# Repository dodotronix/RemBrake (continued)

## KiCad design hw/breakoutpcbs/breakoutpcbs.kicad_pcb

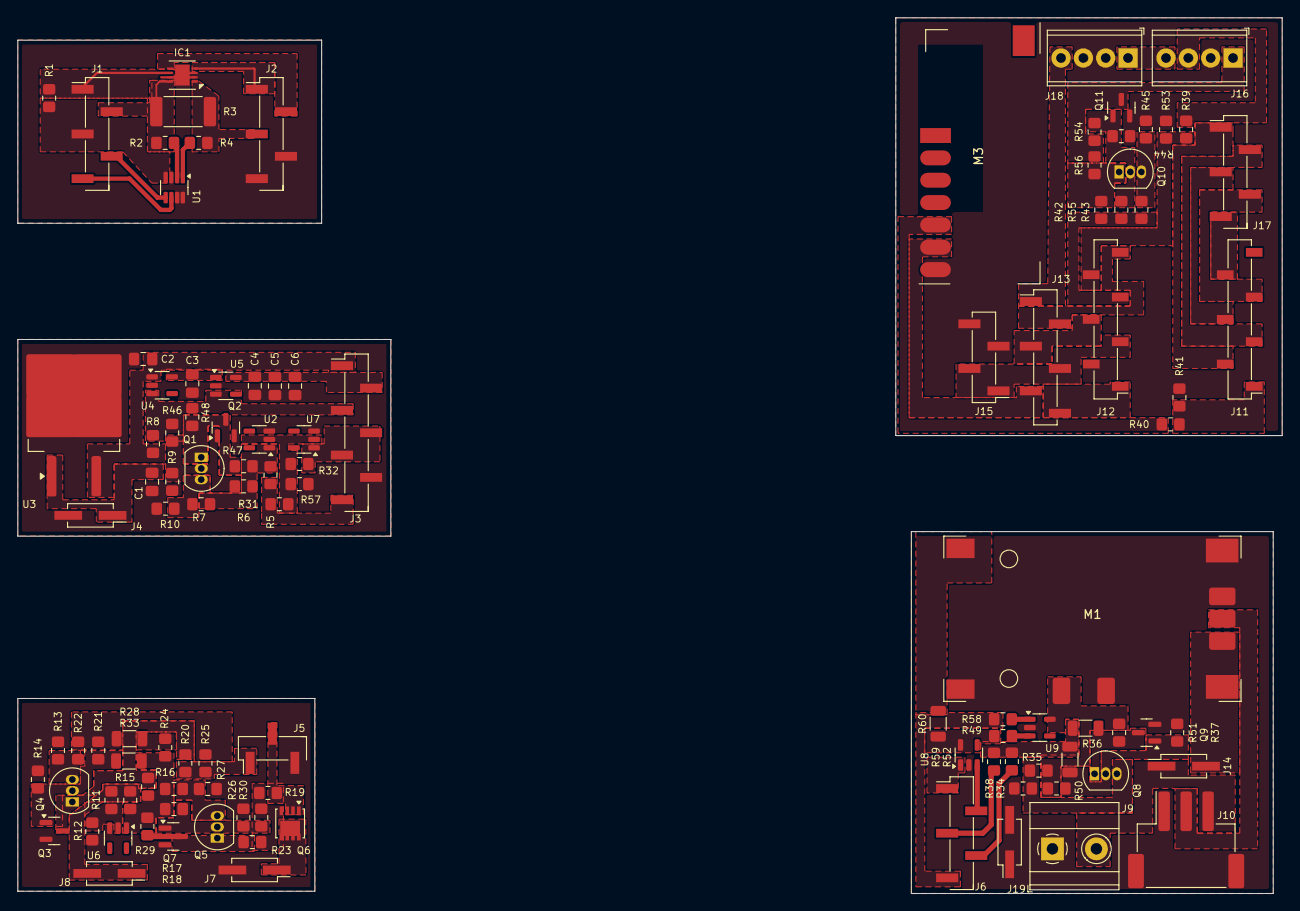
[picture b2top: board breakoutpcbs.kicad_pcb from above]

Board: 2 copper layers, 143.8 x 99.6 mm, 108 parts (0 on the bottom side), 80 nets.

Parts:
C1, C2: 0.1uF; C_0805_2012Metric_Pad1.18x1.45mm_HandSolder
C3: 10uF; C_0805_2012Metric_Pad1.18x1.45mm_HandSolder
C4, C5, C6: 22uF; C_0805_2012Metric_Pad1.18x1.45mm_HandSolder
IC1: LTC2943IDD#TRPBF; DFN-8-1EP_3x3mm_P0.5mm_EP1.66x2.38mm
J1, J2, J6, J17: Conn_01x05; PinHeader_1x05_P2.54mm_Vertical_SMD_Pin1Left
J3: Conn_01x07; PinHeader_1x07_P2.54mm_Vertical_SMD_Pin1Left
J4, J7, J8, J14, J19: Conn_01x02; PinHeader_2x01_P2.54mm_Vertical_SMD
J5: Conn_01x03; PinHeader_1x03_P2.54mm_Vertical_SMD_Pin1Left
J9: Screw_Terminal_01x02; TerminalBlock_Phoenix_MKDS-1,5-2_1x02_P5.00mm_Horizontal
J10: Conn_01x03_MountingPin; JST_XH_S3B-XH-SM4-TB_1x03-1MP_P2.50mm_Horizontal
J11, J12: Conn_01x07; PinSocket_1x07_P2.54mm_Vertical_SMD_Pin1Left
J13: Conn_01x06; PinHeader_1x06_P2.54mm_Vertical_SMD_Pin1Left
J15: Conn_01x04; PinHeader_1x04_P2.54mm_Vertical_SMD_Pin1Left
J16, J18: Screw_Terminal_01x04; TerminalBlock_Phoenix_MPT-0,5-4-2.54_1x04_P2.54mm_Horizontal
M1: USBC_charger
M3: RF_controller
Q1, Q4, Q5, Q8, Q10: BC337; TO-92_Inline
Q2, Q3, Q7, Q9, Q11: BC847; SOT-23
Q6: SiS415DNT; Vishay_PowerPAK_1212-8_Single
R1, R5, R8, R15, R19, R23, R30, R32, R49, R52, R57: 10k; R_0805_2012Metric_Pad1.20x1.40mm_HandSolder
R2, R4: 10; R_0805_2012Metric_Pad1.20x1.40mm_HandSolder
R3: 001R; R_2512_6332Metric_Pad1.40x3.35mm_HandSolder
R6, R7, R10, R13, R16, R20, R24, R25, R27, R31, R38, R45, R46, R47, R48, R54, R56: 0R; R_0805_2012Metric_Pad1.20x1.40mm_HandSolder
R9, R14, R17, R18, R21, R22, R26, R29, R34, R35, R37, R42, R43, R44, R51, R55: 4k2; R_0805_2012Metric_Pad1.20x1.40mm_HandSolder
R11: 91k; R_0805_2012Metric_Pad1.20x1.40mm_HandSolder
R12: 67k; R_0805_2012Metric_Pad1.20x1.40mm_HandSolder
R28, R33, R36, R50, R60: 0R; R_1206_3216Metric
R39: 12k; R_0805_2012Metric_Pad1.20x1.40mm_HandSolder
R40: 2k7; R_0805_2012Metric_Pad1.20x1.40mm_HandSolder
R41, R53: 4k7; R_0805_2012Metric_Pad1.20x1.40mm_HandSolder
R58, R59: 200R; R_0805_2012Metric_Pad1.20x1.40mm_HandSolder
U1: INA219BxDCN; SOT-23-8
U2, U6, U7: BD48ExxG; SOT-23-5
U3: L7805; TO-263-2
U4: XC6220B331MR; SOT-23-5
U5, U8, U9: MAX40200AUK; SOT-23-5

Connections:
+3V3: J1.3, R1.1, U1.4 (VS)
+3V3_1: C4.1, C5.1, C6.1, J3.2, U5.5 (OUT)
+3V3_2: J6.4, R52.1
+3V3_3: J12.3, J13.4, J15.1, J15.2
+5V: C2.1, J3.1, R8.2, U3.3 (OUT), U4.1 (VIN)
+5V_1: J13.5, M3.6 (V+)
+7.5V: J7.1, Q6.5 (D)
+7V5_1: J13.1, J18.4
/battery_charger/CHARGED (GREEN): J6.5, R58.1
/battery_charger/CHARGING (BLUE): J6.3, R59.2
/battery_charger/EN2: J6.2, U8.3 (EN)
/battery_charger/VBUS1: J6.1, U8.1 (VDD)
/break_control/BALARM1: J11.2, J17.1
/break_control/BUTTON: J16.3, R39.1
/break_control/BUZZ: J12.5, R42.1, R43.1, R55.2
/break_control/BUZZER: J16.1, Q11.3 (C), R54.2, R56.2
/break_control/CHARGING1: J12.4, J13.3
/break_control/DCKI: J11.4, J17.3
/break_control/DI: J11.3, J17.2
/break_control/RF SWITCH: J11.1, R40.1, R41.2
/break_control/SCL: J11.6, J17.5
/break_control/SDA: J11.5, J17.4
/break_control/SERVO: J12.7, J13.2
/break_control/VBUS2: J12.1, J13.6
/break_control/VEXT: J16.4, J18.1
/power_manager_bb/BALARM: IC1.6 (~ALCC), J1.1, R1.2
/power_switch_bbA/EN1: J5.1, R20.1, R25.1
/power_switch_bbA/ONOFF: J8.1, J8.2, R11.2, R15.2
/power_switch_bbA/VBATT: J5.2, Q6.1 (S), Q6.2 (S), Q6.3 (S), R19.1
/power_switch_bbB/EN: J3.4, J3.5, R32.1, U7.1 (VOUT)
/power_switch_bbB/ONOFF: C1.1, J4.1, U3.1 (IN)
/power_switch_bbB/RUNNING: J3.3, R8.1, R46.2, R48.2, U4.3 (CE), U5.3 (EN)
/power_switch_bbB/VBUS: J3.7, R5.2, R31.1
GND: IC1.2 (GND_1), IC1.3 (GND_2), IC1.7 (GND_3), IC1.9 (EP), J2.4, J2.5, U1.3 (GND), U1.7 (A0), U1.8 (A1)
GND1: J5.3, J7.2, Q3.2 (E), Q7.2 (E), R12.1, R13.1, R14.1, R26.1, R27.1, U6.3 (GND)
GND2: C1.2, C2.2, C3.2, C4.2, C5.2, C6.2, J3.6, J4.2, Q2.2 (E), R9.1, R10.1, R57.2, U2.3 (GND), U3.2 (GND), U4.2 (GND), U5.2 (GND), U7.3 (GND)
GND3: J9.1, J10.1, J10.MP (MountPin), J19.1, J19.2, M1.2 (GND), M1.5 (BAT-), Q9.2 (E), R37.1, R38.1, U8.2 (GND), U9.2 (GND)
GND4: J12.2, J15.3, J15.4, J16.2, J18.2, J18.3, M3.7 (GND), Q11.2 (E), R41.1, R44.1, R45.1, R53.2
unnamed: IC1.4 (SCL), J2.1
unnamed: IC1.5 (SDA), J2.2
unnamed: IC1.1 (SENSE+), J2.3, R3.2, R4.1
unnamed: IC1.8 (SENSE-), J1.2, R2.1, R3.1
unnamed: J1.4, U1.5 (SCL)
unnamed: J1.5, U1.6 (SDA)
unnamed: J10.2, M1.4 (BM)
unnamed: J9.2, J10.3, J14.1
unnamed: J12.6, R39.2, R53.1
unnamed: J14.2, M1.3 (BAT+)
unnamed: M1.6 (LED), R34.1, R35.1, R51.1, U9.5 (OUT)
unnamed: M1.1 (Vin), R60.1
unnamed: M3.5 (D0), R40.2
unnamed: Q1.2 (B), Q2.1 (B), R6.2, R9.2, R46.1
unnamed: Q1.1 (C), Q2.3 (C), R47.1, R48.1
unnamed: Q1.3 (E), R7.2, R10.2
unnamed: Q3.1 (B), Q4.2 (B), R14.2, R21.2, R33.1
unnamed: Q3.3 (C), Q4.1 (C), R16.1, R20.2
unnamed: Q4.3 (E), R13.2, R22.2
unnamed: Q5.2 (B), Q7.1 (B), R17.2, R26.2, R30.1
unnamed: Q5.1 (C), Q7.3 (C), R23.1, R29.2
unnamed: Q5.3 (E), R18.2, R27.2
unnamed: Q6.4 (G), R19.2, R23.2, R30.2
unnamed: Q8.2 (B), Q9.1 (B), R34.2, R37.2, R50.2
unnamed: Q8.1 (C), Q9.3 (C), R36.2, R51.2
unnamed: Q8.3 (E), R35.2, R38.2
unnamed: Q10.2 (B), Q11.1 (B), R42.2, R44.2, R54.1
unnamed: Q10.1 (C), R55.1, R56.1
unnamed: Q10.3 (E), R43.2, R45.2
unnamed: R21.1, R22.1, R25.2, R28.1
unnamed: R24.1, R28.2
unnamed: R36.1, R50.1, R52.2, R59.1
unnamed: R4.2, U1.1 (IN+)
unnamed: R2.2, U1.2 (IN-)
unnamed: R31.2, R32.2, R57.1, U2.2 (VDD), U7.2 (VDD)
unnamed: R5.1, R6.1, R7.1, R47.2, U2.1 (VOUT)
unnamed: C3.1, U4.5 (VOUT), U5.1 (VDD)
unnamed: R11.1, R12.2, U6.2 (VDD)
unnamed: R15.1, R16.2, R17.1, R18.1, R24.2, R29.1, R33.2, U6.1 (VOUT)
unnamed: R49.1, R60.2, U8.5 (OUT)
unnamed: R49.2, U9.3 (EN)
unnamed: R58.2, U9.1 (VDD)

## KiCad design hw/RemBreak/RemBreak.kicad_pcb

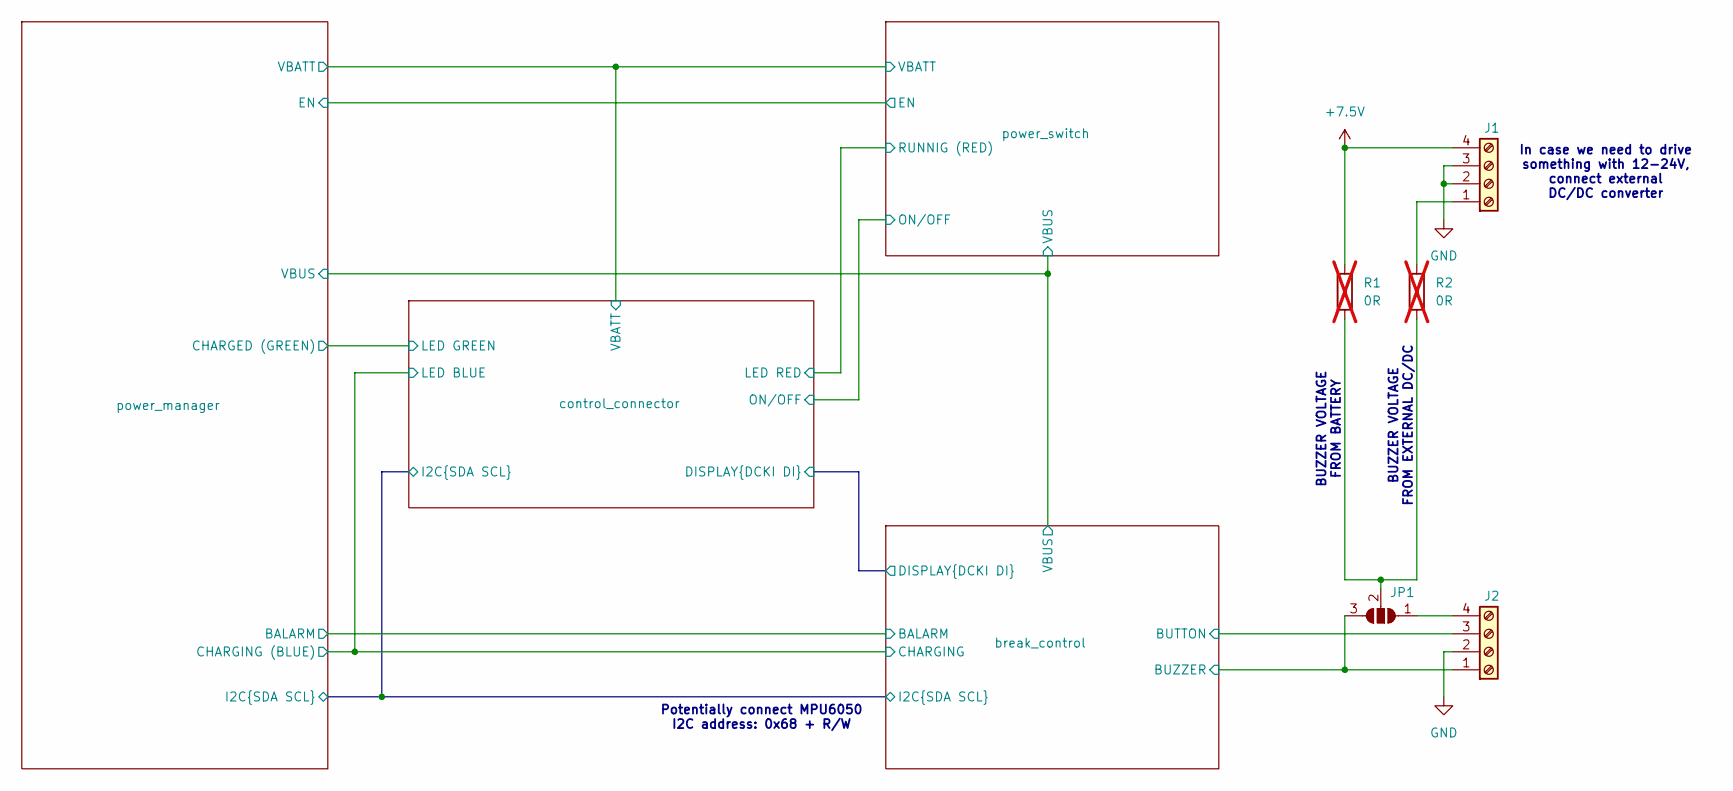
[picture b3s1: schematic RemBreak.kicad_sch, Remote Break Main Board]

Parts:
J1, J2: Screw_Terminal_01x04; TerminalBlock_Phoenix_MPT-0,5-4-2.54_1x04_P2.54mm_Horizontal
JP1: SolderJumper_3_Open; SolderJumper-3_P1.3mm_Open_RoundedPad1.0x1.5mm
R1, R2: 0R; R_0805_2012Metric_Pad1.20x1.40mm_HandSolder; not fitted

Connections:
+7.5V: J1.4, R1.1; also elsewhere on the board
/break_control/BUTTON: J2.3; also elsewhere on the board
/break_control/BUZZER: J2.1, JP1.3 (B); also elsewhere on the board
GND: J1.2, J1.3, J2.2; also elsewhere on the board
unnamed: J1.1, R2.1
unnamed: J2.4, JP1.1 (A)
unnamed: JP1.2 (C), R1.2, R2.2

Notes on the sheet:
Potentially connect MPU6050 I2C address: 0x68 + R/W
BUZZER VOLTAGE FROM BATTERY
BUZZER VOLTAGE FROM EXTERNAL DC/DC
In case we need to drive something with 12-24V, connect external DC/DC converter

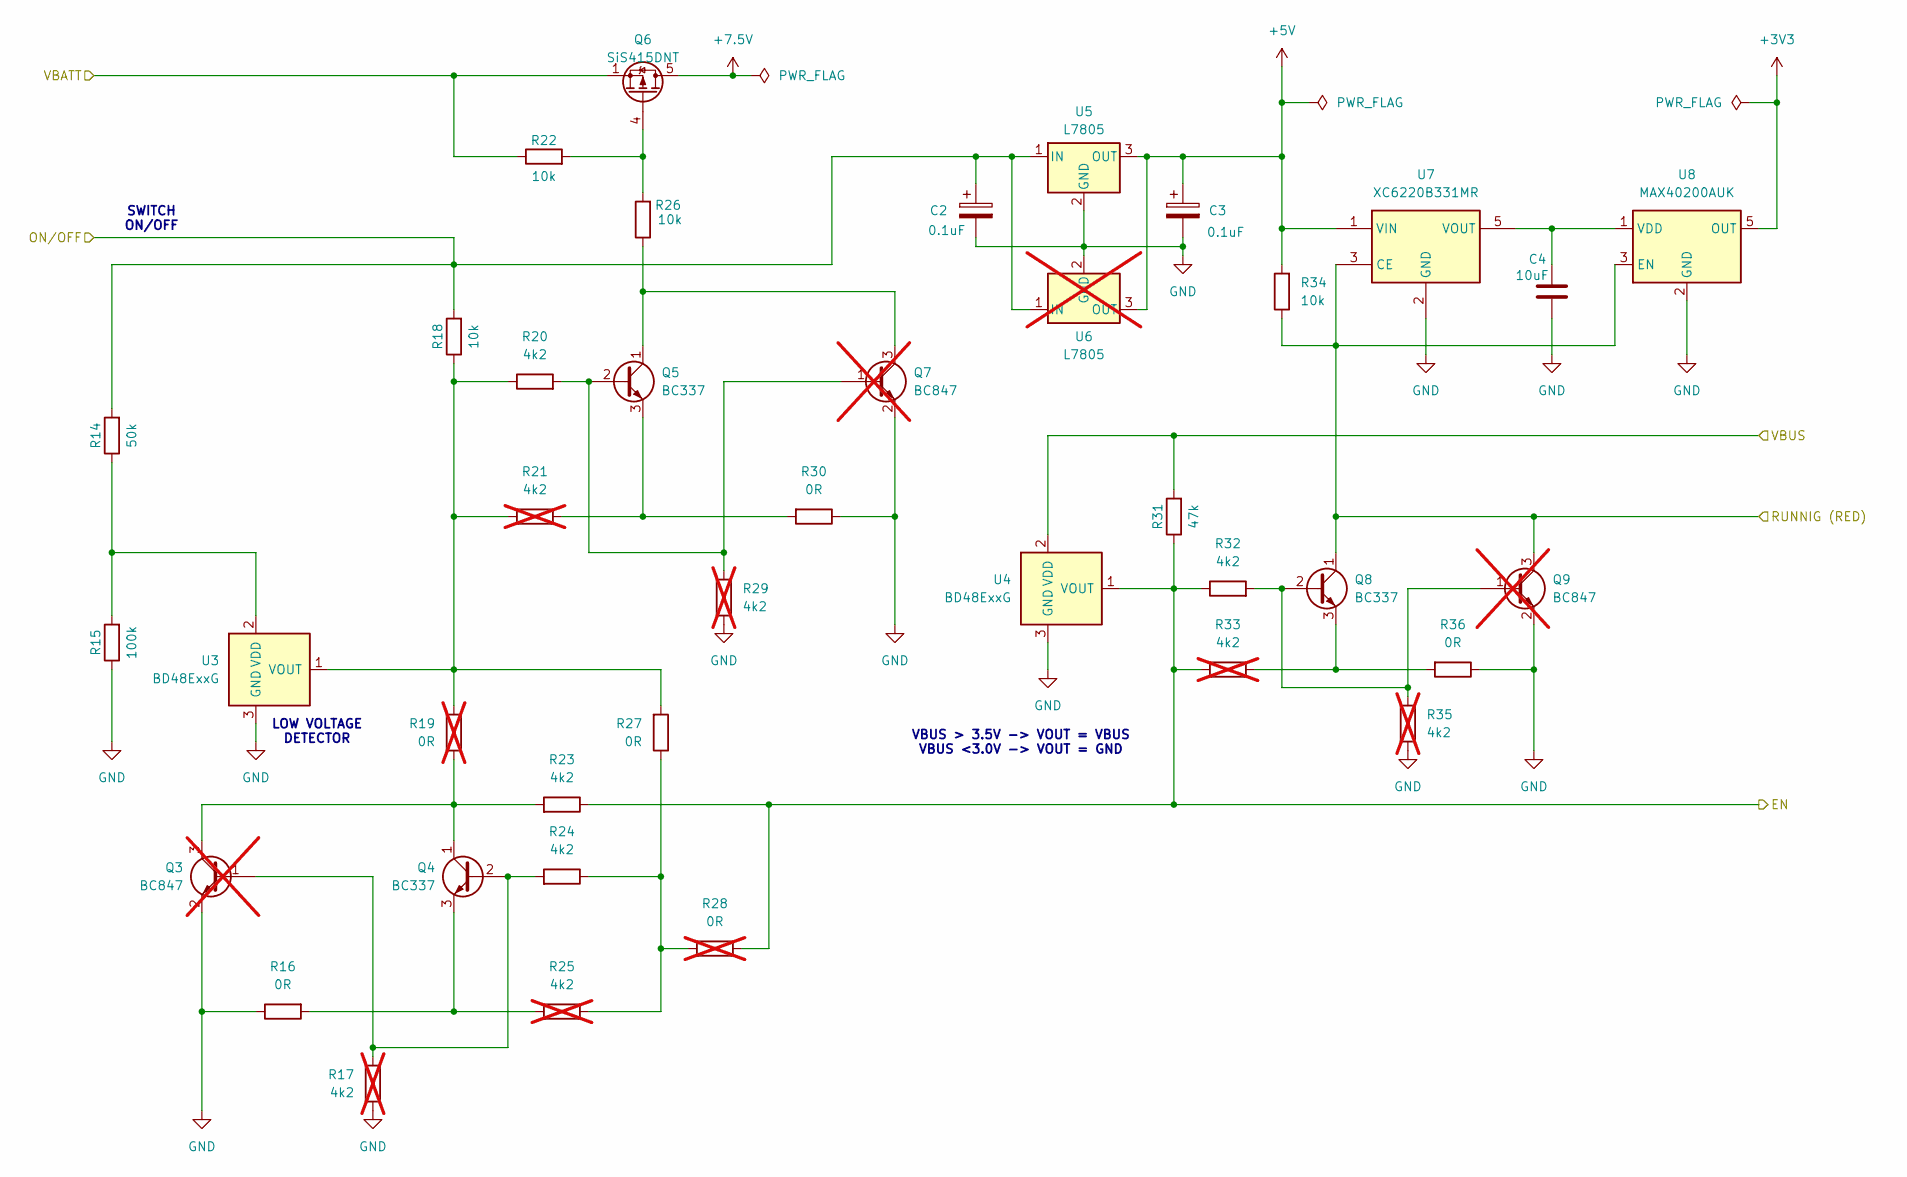
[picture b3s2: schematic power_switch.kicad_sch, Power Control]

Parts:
C2, C3: 0.1uF; C_0805_2012Metric_Pad1.18x1.45mm_HandSolder
C4: 10uF; C_0805_2012Metric_Pad1.18x1.45mm_HandSolder
Q3, Q7, Q9: BC847; SOT-23; not fitted
Q4, Q5, Q8: BC337; TO-92_Inline
Q6: SiS415DNT; Vishay_PowerPAK_1212-8_Single
R14: 50k; R_0805_2012Metric_Pad1.20x1.40mm_HandSolder
R15: 100k; R_0805_2012Metric_Pad1.20x1.40mm_HandSolder
R16, R27, R30, R36: 0R; R_0805_2012Metric_Pad1.20x1.40mm_HandSolder
R17, R21, R25, R29, R33, R35: 4k2; R_0805_2012Metric_Pad1.20x1.40mm_HandSolder; not fitted
R18, R22, R26, R34: 10k; R_0805_2012Metric_Pad1.20x1.40mm_HandSolder
R19, R28: 0R; R_0805_2012Metric_Pad1.20x1.40mm_HandSolder; not fitted
R20, R23, R24, R32: 4k2; R_0805_2012Metric_Pad1.20x1.40mm_HandSolder
R31: 47k; R_0805_2012Metric_Pad1.20x1.40mm_HandSolder
U3, U4: BD48ExxG; SOT-23-5
U5: L7805; TO-263-2
U6: L7805; TO-220-3_Vertical; not fitted
U7: XC6220B331MR; SOT-23-5
U8: MAX40200AUK; SOT-23-5

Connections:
+3V3: U8.5 (OUT); also elsewhere on the board
+5V: C3.1, R34.2, U5.3 (OUT), U6.3 (OUT), U7.1 (VIN); also elsewhere on the board
+7.5V: Q6.5 (D); also elsewhere on the board
/break_control/VBUS: R31.2, U4.2 (VDD); also elsewhere on the board
/control_connector/LED RED: Q8.1 (C), Q9.3 (C), R34.1, U7.3 (CE), U8.3 (EN); also elsewhere on the board
/control_connector/ONOFF: C2.1, R14.2, R18.2, U5.1 (IN), U6.1 (IN); also elsewhere on the board
/control_connector/VBATT: Q6.1 (S), Q6.2 (S), Q6.3 (S), R22.1; also elsewhere on the board
/power_manager/EN: R23.1, R28.1, R31.1, R32.1, R33.1, U4.1 (VOUT); also elsewhere on the board
GND: C2.2, C3.2, C4.2, Q3.2 (E), Q7.2 (E), Q9.2 (E), R15.1, R16.1, R17.1, R29.1, R30.1, R35.1, R36.1, U3.3 (GND), U4.3 (GND), U5.2 (GND), U6.2 (GND), U7.2 (GND), U8.2 (GND); also elsewhere on the board
unnamed: Q3.1 (B), Q4.2 (B), R17.2, R24.2
unnamed: Q3.3 (C), Q4.1 (C), R19.1, R23.2
unnamed: Q4.3 (E), R16.2, R25.2
unnamed: Q5.2 (B), Q7.1 (B), R20.2, R29.2
unnamed: Q5.1 (C), Q7.3 (C), R26.1
unnamed: Q5.3 (E), R21.2, R30.2
unnamed: Q6.4 (G), R22.2, R26.2
unnamed: Q8.2 (B), Q9.1 (B), R32.2, R35.2
unnamed: Q8.3 (E), R33.2, R36.2
unnamed: R24.1, R25.1, R27.1, R28.2
unnamed: R14.1, R15.2, U3.2 (VDD)
unnamed: R18.1, R19.2, R20.1, R21.1, R27.2, U3.1 (VOUT)
unnamed: C4.1, U7.5 (VOUT), U8.1 (VDD)

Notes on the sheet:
VBUS > 3.5V -> VOUT = VBUS VBUS <3.0V -> VOUT = GND
LOW VOLTAGE DETECTOR
SWITCH ON/OFF

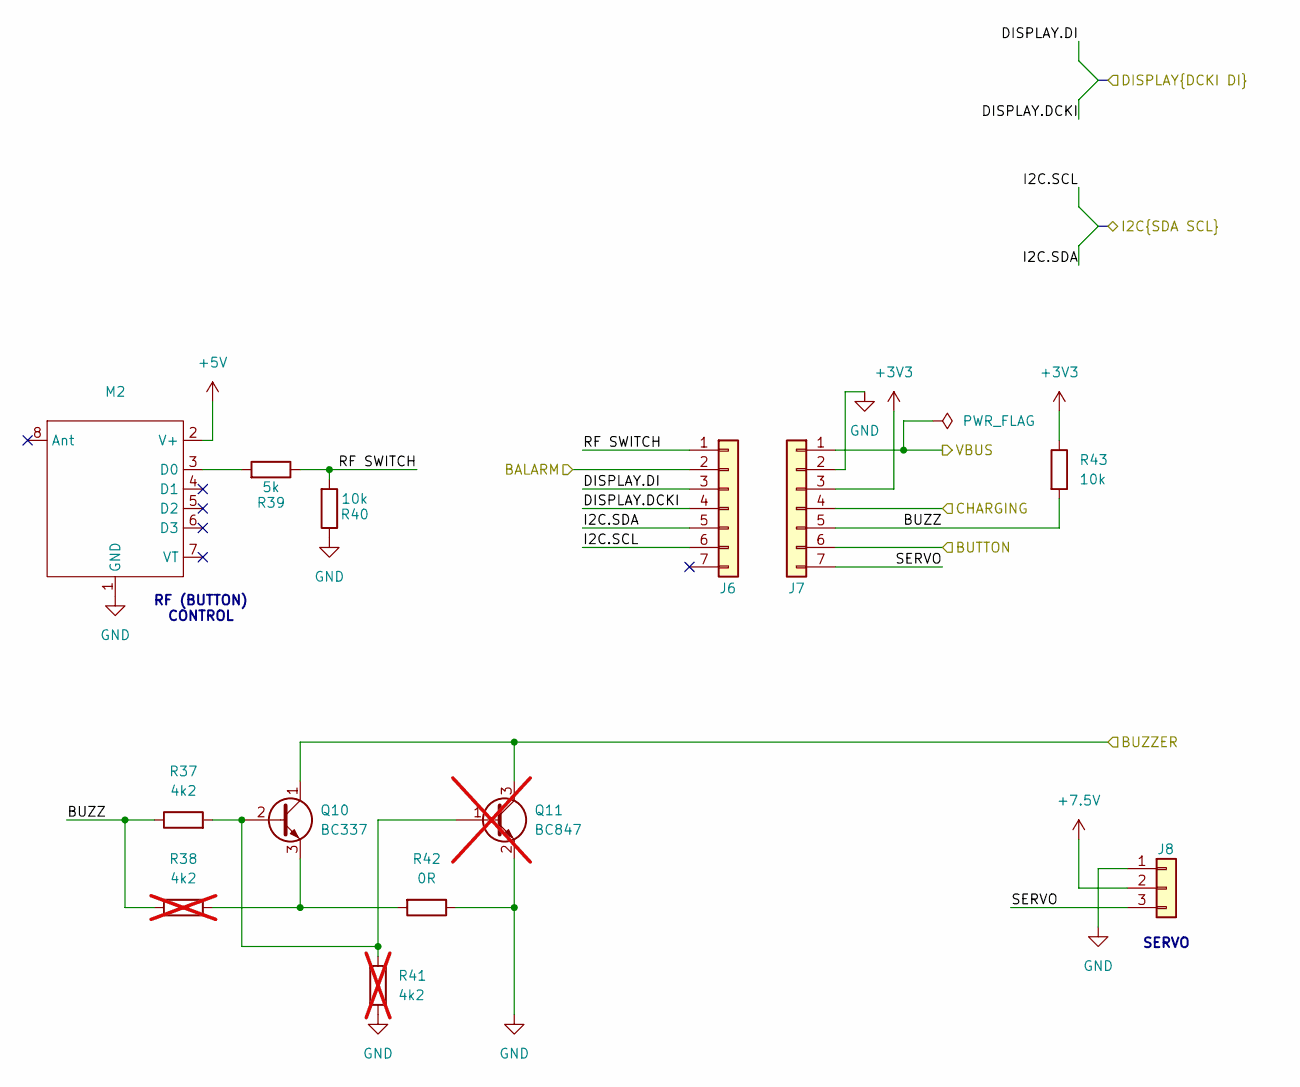
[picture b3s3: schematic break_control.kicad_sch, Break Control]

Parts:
J6, J7: Conn_01x07; PinSocket_1x07_P2.54mm_Vertical_SMD_Pin1Left
J8: Conn_01x03; PinHeader_1x03_P2.54mm_Vertical_SMD_Pin1Left
M2: RF_controller
Q10: BC337; TO-92_Inline
Q11: BC847; SOT-23; not fitted
R37: 4k2; R_0805_2012Metric_Pad1.20x1.40mm_HandSolder
R38, R41: 4k2; R_0805_2012Metric_Pad1.20x1.40mm_HandSolder; not fitted
R39: 5k; R_0805_2012Metric_Pad1.20x1.40mm_HandSolder
R40, R43: 10k; R_0805_2012Metric_Pad1.20x1.40mm_HandSolder
R42: 0R; R_0805_2012Metric_Pad1.20x1.40mm_HandSolder

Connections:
+3V3: J7.3, R43.1; also elsewhere on the board
+5V: M2.2 (V+); also elsewhere on the board
+7.5V: J8.2; also elsewhere on the board
/break_control/BALARM: J6.2; also elsewhere on the board
/break_control/BUTTON: J7.6; also elsewhere on the board
/break_control/BUZZ: J7.5, R37.1, R38.1, R43.2
/break_control/BUZZER: Q10.1 (C), Q11.3 (C); also elsewhere on the board
/break_control/DISPLAY.DCKI: J6.4; also elsewhere on the board
/break_control/DISPLAY.DI: J6.3; also elsewhere on the board
/break_control/I2C.SCL: J6.6; also elsewhere on the board
/break_control/I2C.SDA: J6.5; also elsewhere on the board
/break_control/RF SWITCH: J6.1, R39.1, R40.2
/break_control/SERVO: J7.7, J8.3
/break_control/VBUS: J7.1; also elsewhere on the board
/control_connector/LED BLUE: J7.4; also elsewhere on the board
GND: J7.2, J8.1, M2.1 (GND), Q11.2 (E), R40.1, R41.1, R42.1; also elsewhere on the board
unnamed: M2.3 (D0), R39.2
unnamed: Q10.2 (B), Q11.1 (B), R37.2, R41.2
unnamed: Q10.3 (E), R38.2, R42.2

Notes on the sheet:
SERVO
RF (BUTTON) CONTROL

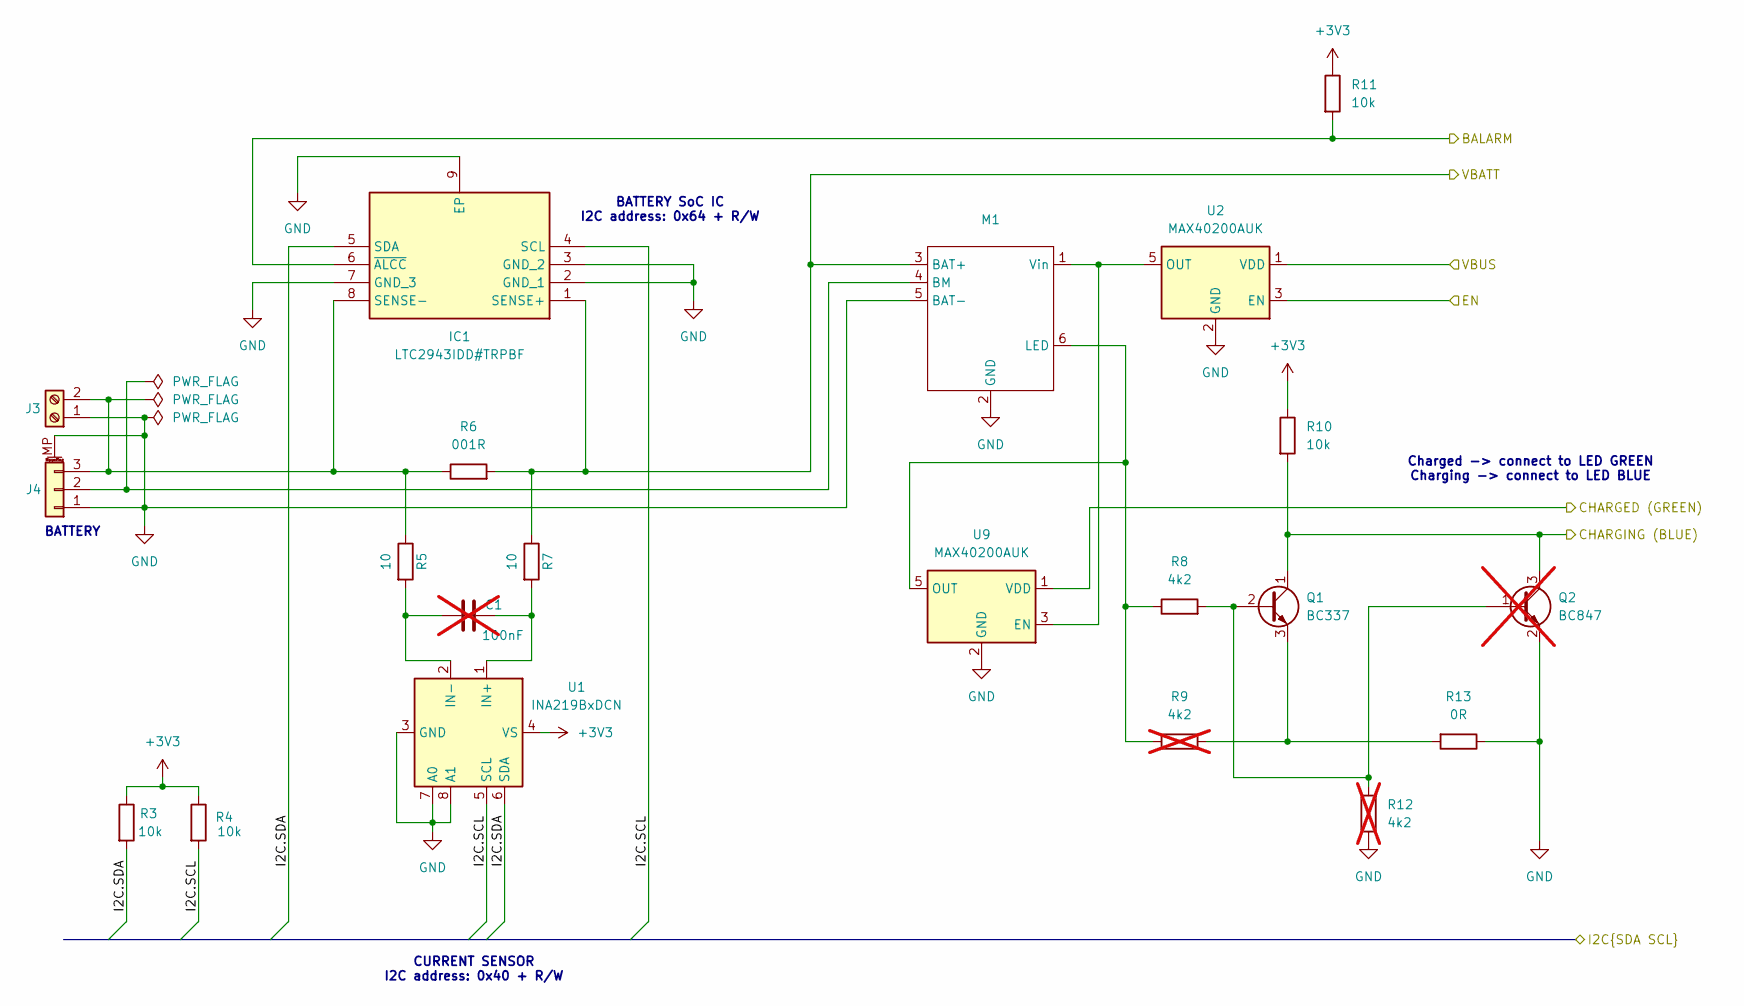
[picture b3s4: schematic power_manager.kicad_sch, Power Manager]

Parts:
C1: 100nF; C_0805_2012Metric_Pad1.18x1.45mm_HandSolder; not fitted
IC1: LTC2943IDD#TRPBF; DFN-8-1EP_3x3mm_P0.5mm_EP1.66x2.38mm; Mouser Part Number 584-LTC2943IDD#TRPBF
J3: Screw_Terminal_01x02; TerminalBlock_Phoenix_MKDS-1,5-2_1x02_P5.00mm_Horizontal
J4: Conn_01x03_MountingPin; JST_XH_S3B-XH-SM4-TB_1x03-1MP_P2.50mm_Horizontal
M1: USBC_charger
Q1: BC337; TO-92_Inline
Q2: BC847; SOT-23; not fitted
R3, R4, R10, R11: 10k; R_0805_2012Metric_Pad1.20x1.40mm_HandSolder
R5, R7: 10; R_0805_2012Metric_Pad1.20x1.40mm_HandSolder
R6: 001R; R_2512_6332Metric_Pad1.40x3.35mm_HandSolder
R8: 4k2; R_0805_2012Metric_Pad1.20x1.40mm_HandSolder
R9, R12: 4k2; R_0805_2012Metric_Pad1.20x1.40mm_HandSolder; not fitted
R13: 0R; R_0805_2012Metric_Pad1.20x1.40mm_HandSolder
U1: INA219BxDCN; SOT-23-8
U2, U9: MAX40200AUK; SOT-23-5

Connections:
+3V3: R3.1, R4.1, R10.1, R11.1, U1.4 (VS); also elsewhere on the board
/break_control/BALARM: IC1.6 (~ALCC), R11.2; also elsewhere on the board
/break_control/I2C.SCL: IC1.4 (SCL), R4.2, U1.5 (SCL); also elsewhere on the board
/break_control/I2C.SDA: IC1.5 (SDA), R3.2, U1.6 (SDA); also elsewhere on the board
/break_control/VBUS: U2.1 (VDD); also elsewhere on the board
/control_connector/LED BLUE: Q1.1 (C), Q2.3 (C), R10.2; also elsewhere on the board
/control_connector/VBATT: IC1.1 (SENSE+), M1.3 (BAT+), R6.2, R7.1; also elsewhere on the board
/power_manager/EN: U2.3 (EN); also elsewhere on the board
GND: IC1.2 (GND_1), IC1.3 (GND_2), IC1.7 (GND_3), IC1.9 (EP), J3.1, J4.1, J4.MP (MountPin), M1.2 (GND), M1.5 (BAT-), Q2.2 (E), R12.1, R13.1, U1.3 (GND), U1.7 (A0), U1.8 (A1), U2.2 (GND), U9.2 (GND); also elsewhere on the board
unnamed: IC1.8 (SENSE-), J3.2, J4.3, R5.1, R6.1
unnamed: J4.2, M1.4 (BM)
unnamed: M1.1 (Vin), U2.5 (OUT), U9.3 (EN)
unnamed: Q1.2 (B), Q2.1 (B), R8.2, R12.2
unnamed: Q1.3 (E), R9.2, R13.2
unnamed: C1.2, R7.2, U1.1 (IN+)
unnamed: C1.1, R5.2, U1.2 (IN-)

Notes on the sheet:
CURRENT SENSOR I2C address: 0x40 + R/W
BATTERY SoC IC I2C address: 0x64 + R/W
Charged -> connect to LED GREEN Charging -> connect to LED BLUE
BATTERY

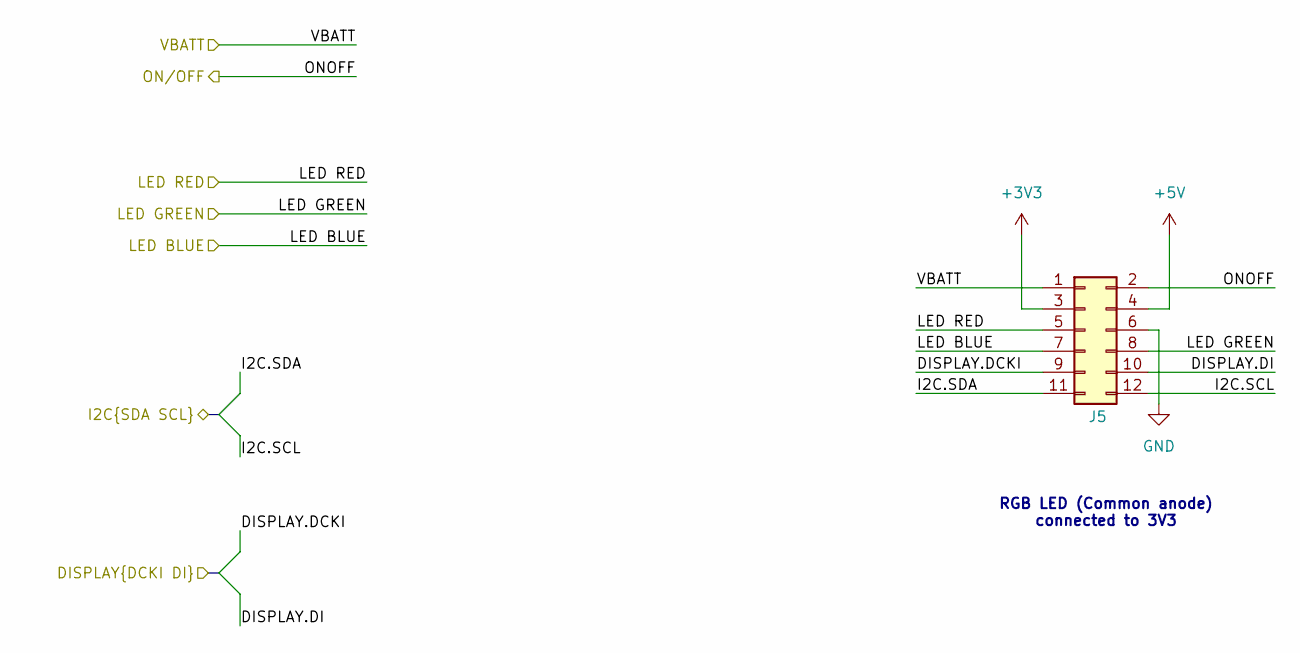
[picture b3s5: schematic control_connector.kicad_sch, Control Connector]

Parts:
J5: Conn_02x06_Odd_Even; SAMTEC_TSM-106-01-L-DH-P-TR

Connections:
+3V3: J5.3; also elsewhere on the board
+5V: J5.4; also elsewhere on the board
/break_control/DISPLAY.DCKI: J5.9; also elsewhere on the board
/break_control/DISPLAY.DI: J5.10; also elsewhere on the board
/break_control/I2C.SCL: J5.12; also elsewhere on the board
/break_control/I2C.SDA: J5.11; also elsewhere on the board
/control_connector/LED BLUE: J5.7; also elsewhere on the board
/control_connector/LED RED: J5.5; also elsewhere on the board
/control_connector/ONOFF: J5.2; also elsewhere on the board
/control_connector/VBATT: J5.1; also elsewhere on the board
GND: J5.6; also elsewhere on the board

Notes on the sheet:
RGB LED (Common anode) connected to 3V3

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
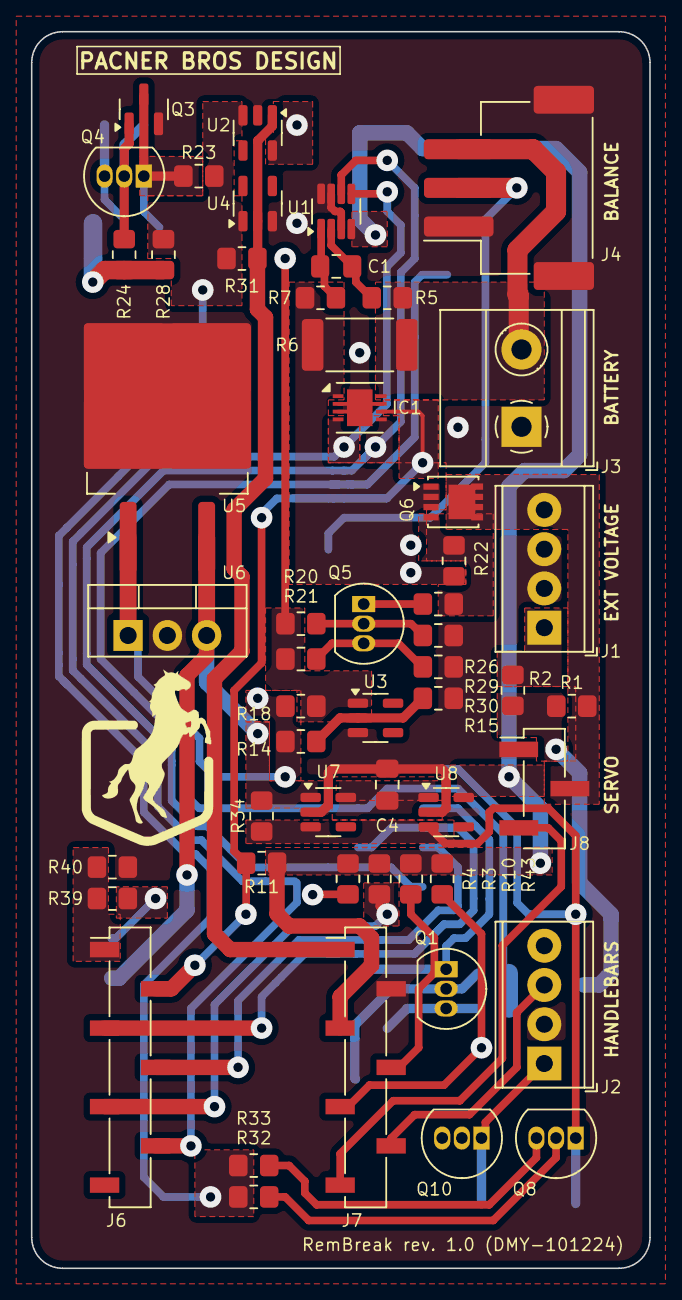
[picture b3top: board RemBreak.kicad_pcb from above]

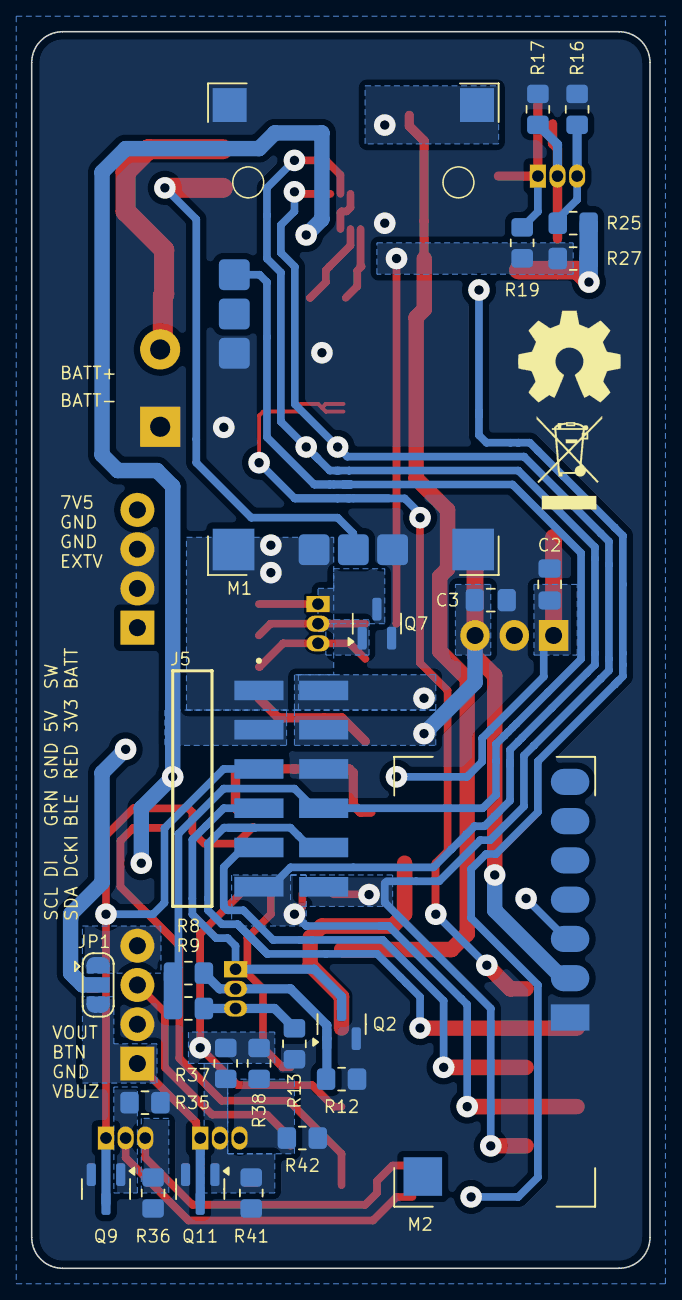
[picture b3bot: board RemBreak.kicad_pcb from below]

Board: 2 copper layers, 40.0 x 80.0 mm, 78 parts (25 on the bottom side), 47 nets.

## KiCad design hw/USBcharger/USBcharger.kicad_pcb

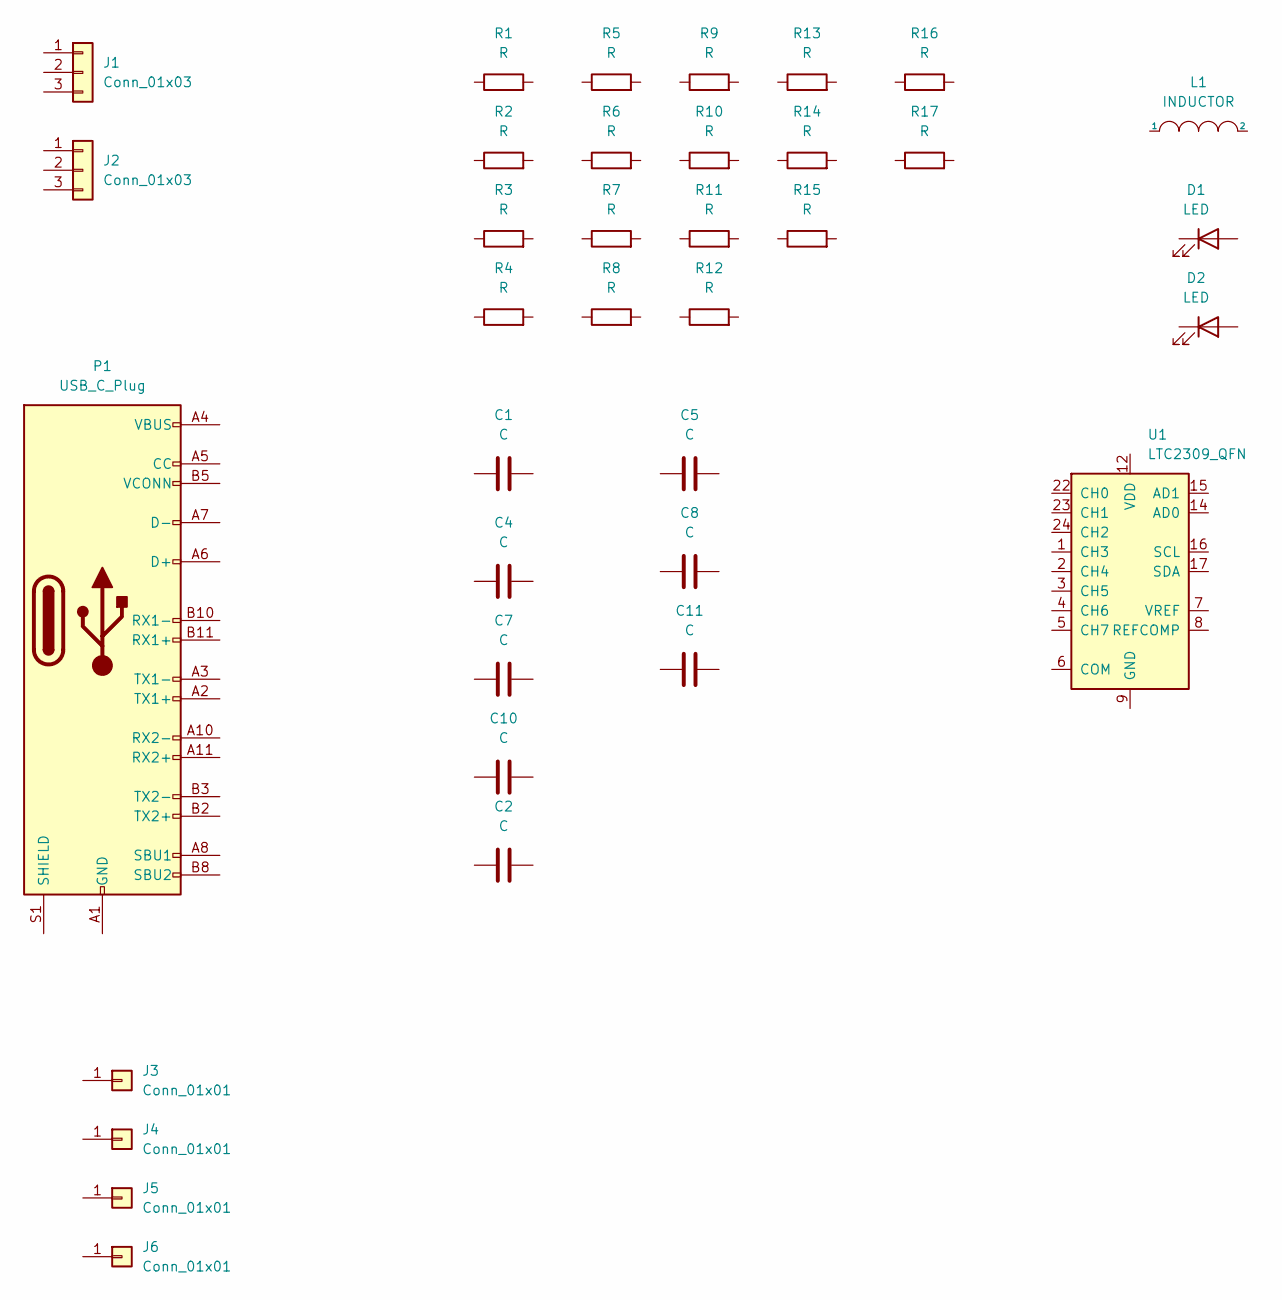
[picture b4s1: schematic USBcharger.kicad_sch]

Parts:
C1, C2, C4: C; C_0603_1608Metric
C5, C7, C8, C10, C11: C; C_0805_2012Metric
D1, D2: LED; LED_0603_1608Metric
J1, J2: Conn_01x03; PinHeader_1x03_P2.54mm_Vertical
J3, J4: Conn_01x01; TestPoint_THTPad_2.0x2.0mm_Drill1.0mm
J5, J6: Conn_01x01; TestPoint_THTPad_2.5x2.5mm_Drill1.2mm
L1: INDUCTOR; L_APV_APH0620
P1: USB_C_Plug; USB_C_Receptacle_GCT_USB4105-xx-A_16P_TopMnt_Horizontal
R1, R2, R3, R4, R5, R6, R7, R8, R9, R10, R11, R12, R13, R14, R15: R; R_0603_1608Metric
R16, R17: R; R_0805_2012Metric
U1: LTC2309_QFN; QFN-24-1EP_4x4mm_P0.5mm_EP2.6x2.6mm

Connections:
unnamed: P1.A1 (GND), P1.A12 (GND), P1.B1 (GND), P1.B12 (GND)
unnamed: P1.A4 (VBUS), P1.A9 (VBUS), P1.B4 (VBUS), P1.B9 (VBUS)
unnamed: U1.9 (GND), U1.10 (GND), U1.11 (GND), U1.18 (GND), U1.19 (GND), U1.20 (GND), U1.25 (GND)
unnamed: U1.12 (VDD), U1.13 (VDD), U1.21 (VDD)

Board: 11 copper layers, 36 parts (0 on the bottom side), 4 nets, no tracks yet.

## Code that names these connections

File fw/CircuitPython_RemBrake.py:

import asyncio
import pwmio
import simpleio
import keypad

from adafruit_motor import servo
from digitalio import DigitalInOut, Direction

from CircuitPython_LTC2943 import Mode, Prescaler

class BatteryMonitor():
    def __init__(self, bms, display, charging_pin=None, buzzer=None) -> None:
        self.bms = bms
        self.display = display
        self.buzzer = buzzer
        # simpleio.tone(board.D9, 440, duration=1.0)
        self._charging_pin = DigitalInOut(charging_pin)
        self._charging_pin.direction = Direction.INPUT
        self._number_of_steps = display.get_number_of_segments()
        self._charge_step = ((bms.charge_range[1] - bms.charge_range[0]) 
                            / self._number_of_steps)
        # DEBUG
        print("")
        print(self.bms.temperature)
        print(self.bms.accumulated_charge)

        # INIT
        self.bms.adc_mode = Mode.AUTOMATIC
        self.bms.prescaler = Prescaler.PRES_M64

    async def status(self):
        while True:
            # LOCK the routine until it gets the data ?
            cstatus = self.bms.accumulated_charge
            level = int(cstatus / self._charge_step)
            self.display.bits = 0x3ff >> (self._number_of_steps - level)
            print(cstatus, self.bms.temperature, level, self.bms.current)
            await asyncio.sleep(0.5)

class BreakController():
    def __init__(self, servo_pin,  remote_button, wired_button, test_pin) -> None:
        self._pwm = pwmio.PWMOut(servo_pin, duty_cycle=2 ** 15, frequency=50)
        self._servo = servo.Servo(self._pwm)
        self.test_pin = DigitalInOut(test_pin)
        self.test_pin.direction = Direction.OUTPUT
        self.test_pin.value = False

        self._keys = keypad.Keys((remote_button, wired_button),
                                 value_when_pressed=True, pull=False)

    # TODO reset servo position to the state, where it detects the pressure 
    # TODO then define how the button 0 should behave
    # TODO steps and intervals to break for the button 1???

    async def active(self):
        while True:
            event = self._keys.events.get()
            if event:
                # print(event.pressed)
                print(event)
            await asyncio.sleep(0.1)
